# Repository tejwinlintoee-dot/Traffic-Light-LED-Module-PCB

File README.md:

# 🚦 Traffic Light LED Module PCB

A custom Traffic Light LED Indicator PCB designed using KiCad.

## Overview

This project consists of a compact three-LED indicator module featuring:

- 🔴 Red LED
- 🟡 Yellow LED
- 🟢 Green LED

Each LED is driven through a 220 Ω current-limiting resistor and connected through a 4-pin header interface.

## Features

- Custom PCB designed in KiCad 10
- Compact PCB layout
- 4-pin connector interface
- 220 Ω current-limiting resistors
- ERC verified
- DRC verified
- 3D visualization completed
- Suitable for embedded systems and microcontroller projects

## PCB Layout

## 3D View

## 3D View (With Components)

## Schematic

## Hardware Specifications

| Component | Quantity |
|------------|----------|
| Red LED | 1 |
| Yellow LED | 1 |
| Green LED | 1 |
| 220 Ω Resistor | 3 |
| 1×4 Header Connector | 1 |

## Project Files

- PCB Layout (`.kicad_pcb`)
- Schematic (`.kicad_sch`)
- KiCad Project (`.kicad_pro`)

## Tools Used

- KiCad 10
- GitHub

## Applications

- Traffic Light Simulation
- Embedded Systems Projects
- Microcontroller Learning
- Electronics Education
- Status Indicator Modules

## Author

**Tejwin Linto**

Electrical and Electronics Engineering Student

### Areas of Interest

- Embedded Systems
- PCB Design
- IoT Development
- Hardware Design
- Microcontrollers
- Electric Vehicles

## Repository Structure

```text
Traffic-Light-LED-Module-PCB
│
├── README.md
├── LICENSE
│
└── KiCad
    ├── traffic light module.kicad_pcb.kicad_pcb
    ├── traffic light module.kicad_pro.kicad_pro
    ├── traffic light module.kicad_sch.kicad_sch
    ├── pcb-layout.png
    ├── pcb-3d-view.png
    ├── pcb-3d-view-components.png
    └── schematic.png
```

## License

This project is licensed under the MIT License.

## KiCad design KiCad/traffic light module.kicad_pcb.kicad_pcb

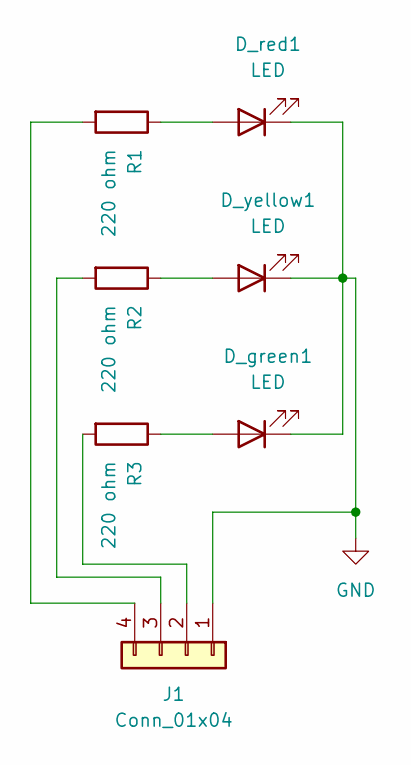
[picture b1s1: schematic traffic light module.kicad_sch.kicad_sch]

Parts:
D_green1: LED; LED_D10.0mm
D_red1: LED; LED_D10.0mm
D_yellow1: LED; LED_D10.0mm
J1: Conn_01x04; PinHeader_1x04_P2.54mm_Horizontal
R1, R2, R3: 220 ohm; R_0805_2012Metric

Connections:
GND: D_green1.1 (K), D_red1.1 (K), D_yellow1.1 (K), J1.1
unnamed: D_green1.2 (A), R3.1
unnamed: D_red1.2 (A), R1.1
unnamed: D_yellow1.2 (A), R2.1
unnamed: J1.2, R3.2
unnamed: J1.3, R2.2
unnamed: J1.4, R1.2

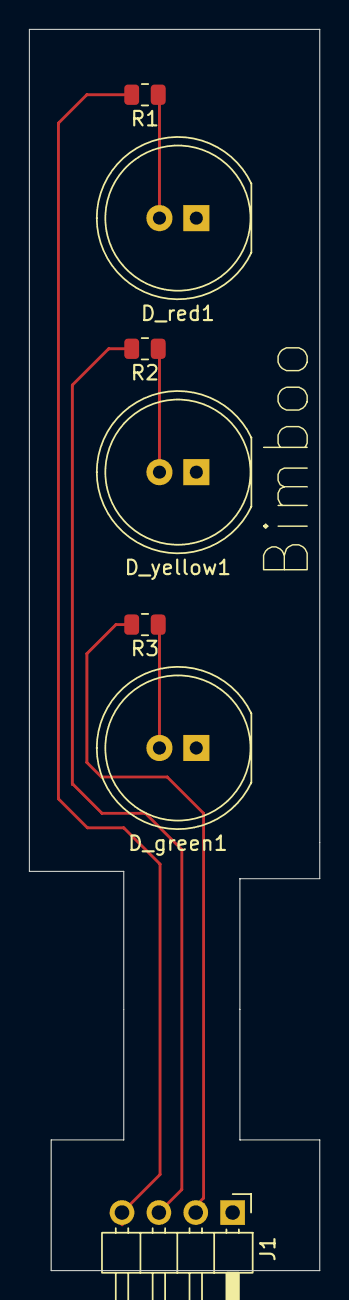
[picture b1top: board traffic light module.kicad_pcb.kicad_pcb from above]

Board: 2 copper layers, 20.0 x 85.5 mm, 7 parts (0 on the bottom side), 7 nets.

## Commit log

2026-06-20 Create Traffic-Light-LED-Module-PCB
2026-06-20 Create Traffic-Light-LED-Module-PCB-DESIGN
2026-06-20 Add new 3D view image for components
2026-06-20 Add additional 3D view image to README
2026-06-20 Fix formatting of '1x4 Header Connector' in README
